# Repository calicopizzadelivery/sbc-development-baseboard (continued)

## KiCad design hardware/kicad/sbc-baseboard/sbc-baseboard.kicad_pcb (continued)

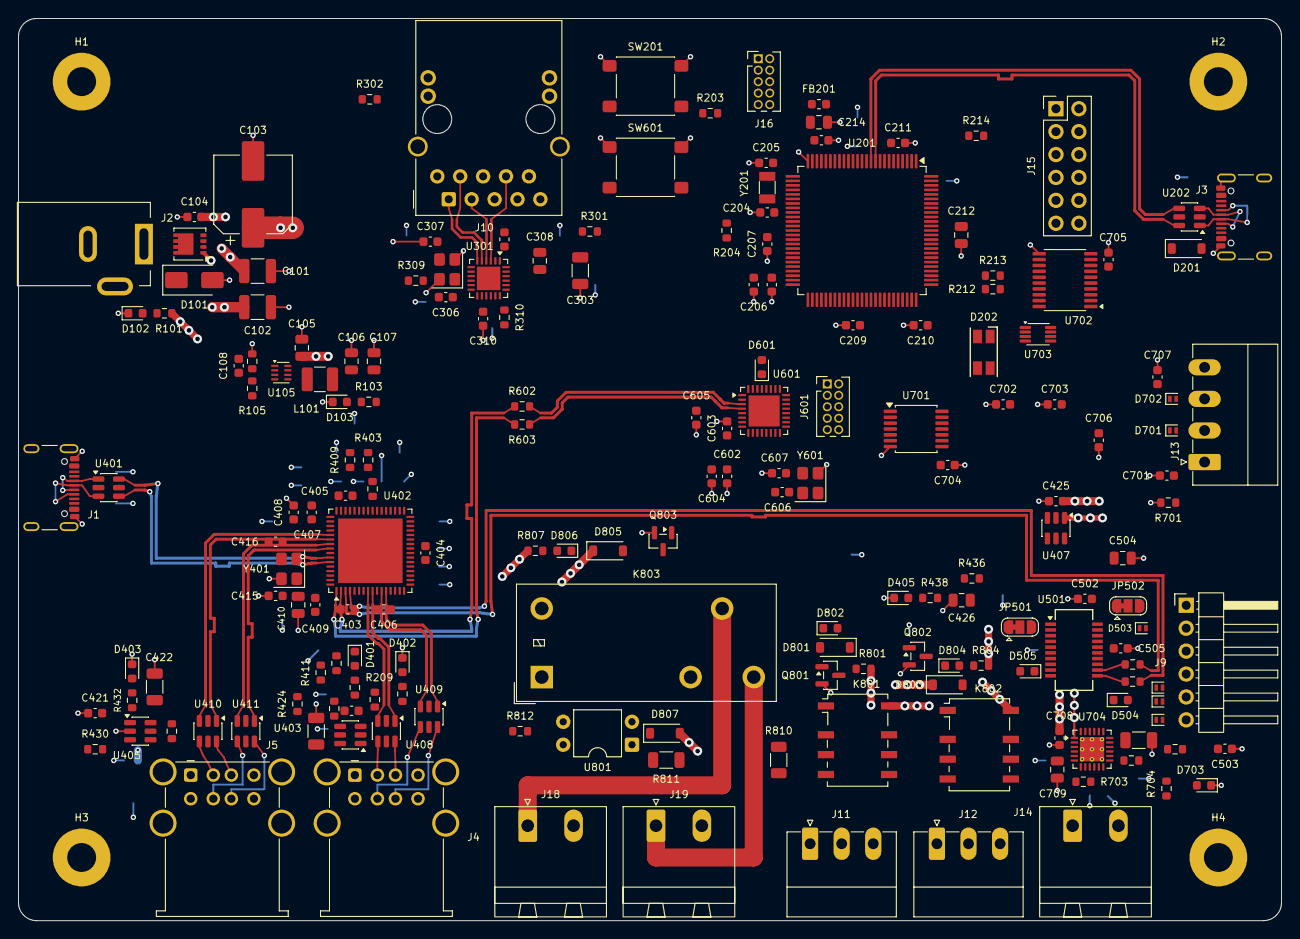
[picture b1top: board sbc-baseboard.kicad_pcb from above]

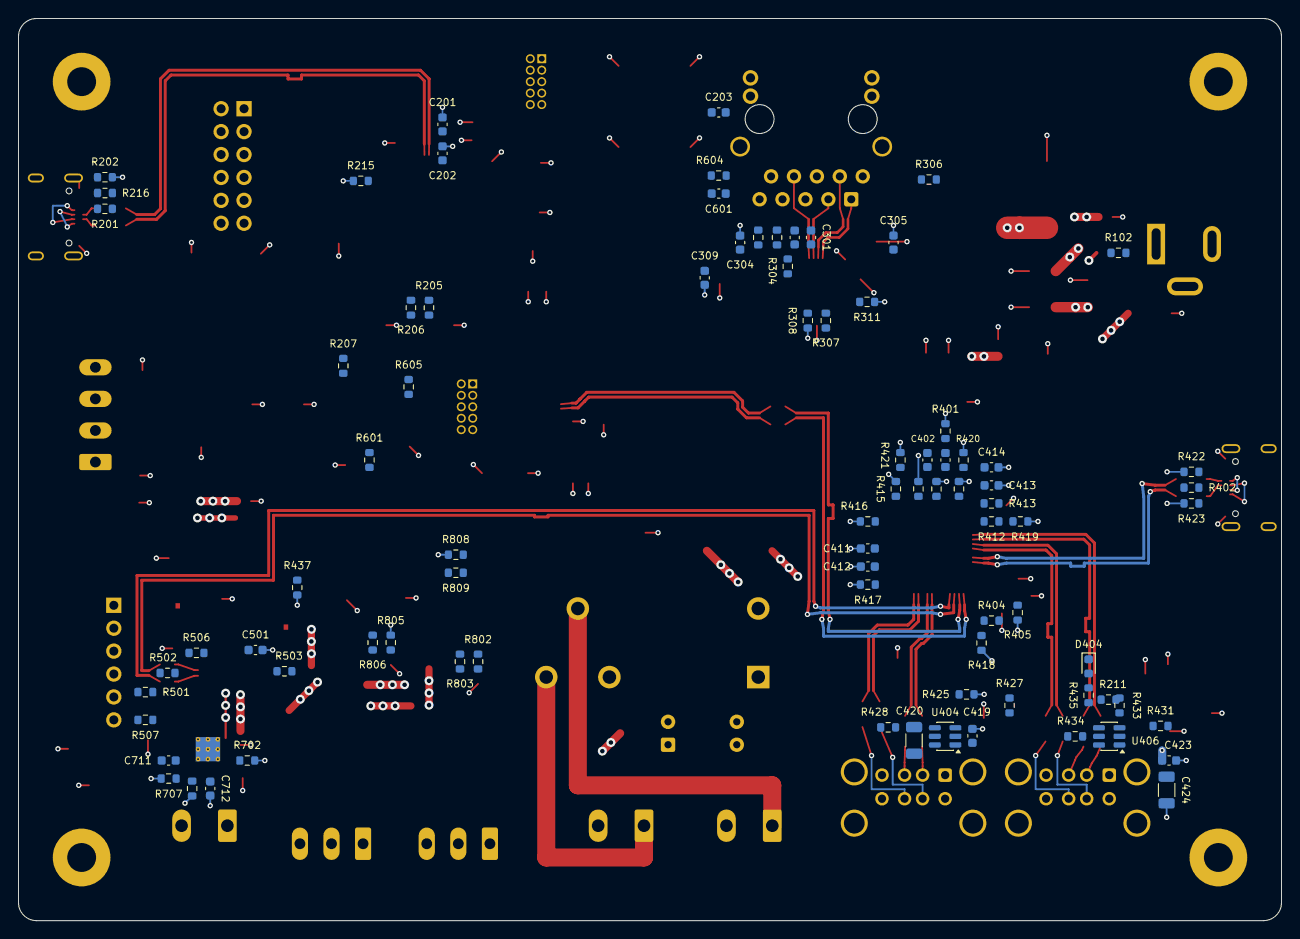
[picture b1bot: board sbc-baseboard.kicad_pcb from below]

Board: 6 copper layers, 140.0 x 100.0 mm, 271 parts (84 on the bottom side), 222 nets.

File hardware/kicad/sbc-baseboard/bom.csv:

"Reference","Value","Footprint","QUANTITY"
"C101,C102","47u/10V","Capacitor_SMD:C_1210_3225Metric","2"
"C103","100u/10V","Capacitor_SMD:CP_Elec_8x10.5","1"
"C104,C206,C207,C208,C209,C210,C211,C213,C301,C302,C305,C309,C310,C403,C404,C405,C406,C407,C408,C409,C412,C414,C417,C419,C421,C423,C425,C501,C505,C601,C603,C604,C701,C702,C703,C704,C705,C706,C707,C708","100n","Capacitor_SMD:C_0603_1608Metric","40"
"C105,C212,C214,C426,C504,C709","10u","Capacitor_SMD:C_0805_2012Metric","6"
"C106,C107,C308","22u","Capacitor_SMD:C_0805_2012Metric","3"
"C108","120p","Capacitor_SMD:C_0603_1608Metric","1"
"C201,C202,C304,C602,C605","2u2","Capacitor_SMD:C_0603_1608Metric","5"
"C203,C401,C402,C411,C413","1u","Capacitor_SMD:C_0603_1608Metric","5"
"C204,C205","12p","Capacitor_SMD:C_0603_1608Metric","2"
"C303","1n/2kV","Capacitor_SMD:C_1206_3216Metric","1"
"C306,C307","22p","Capacitor_SMD:C_0603_1608Metric","2"
"C410","4u7","Capacitor_SMD:C_0805_2012Metric","1"
"C415,C416","33p","Capacitor_SMD:C_0603_1608Metric","2"
"C418,C420,C422,C424,C710","22u","Capacitor_SMD:C_1206_3216Metric","5"
"C502,C503","47p","Capacitor_SMD:C_0603_1608Metric","2"
"C606,C607","18p","Capacitor_SMD:C_0603_1608Metric","2"
"C711","1n","Capacitor_SMD:C_0603_1608Metric","1"
"C712","10n","Capacitor_SMD:C_0603_1608Metric","1"
"D101","SMAJ5.0A","Diode_SMD:D_SMA","1"
"D102,D103","LED AMBER","LED_SMD:LED_0603_1608Metric","2"
"D201","BAT54","Diode_SMD:D_SOD-123","1"
"D202","RGB heartbeat","LED_SMD:LED_RGB_1210","1"
"D401,D402,D403,D404,D405,D504,D505,D601,D703","LED GREEN","LED_SMD:LED_0603_1608Metric","9"
"D501,D502,D503,D506,D701,D702","PESD5V0S1UL","Diode_SMD:D_SOD-882","6"
"D801,D803,D805,D807","1N4148W","Diode_SMD:D_SOD-123","4"
"D802,D804,D806","LED RED","LED_SMD:LED_0603_1608Metric","3"
"FB201,FB301","600R@100MHz","Inductor_SMD:L_0603_1608Metric","2"
"H1,H2,H3,H4","M3","MountingHole:MountingHole_3.2mm_M3_Pad","4"
"J1","USB-C upstream","calico:USB_C_Receptacle_GCT_USB4105-xx-A_16P_TopMnt_Horizontal_PegClear","1"
"J2","5 V in, 2.5 mm","Connector_BarrelJack:BarrelJack_Kycon_KLDX-0202-xC_Horizontal","1"
"J3","USB-C HID to target","calico:USB_C_Receptacle_GCT_USB4105-xx-A_16P_TopMnt_Horizontal_PegClear","1"
"J4,J5","USB-A x2","Connector_USB:USB_A_Wuerth_61400826021_Horizontal_Stacked","2"
"J9","FTDI header","Connector_PinHeader_2.54mm:PinHeader_1x06_P2.54mm_Horizontal","1"
"J10","RJ45 magjack 10/100","Connector_RJ:RJ45_Kycon_G7LX-A88S7-BP-xx_Horizontal","1"
"J11,J12","COM/NO/NC","Connector_Phoenix_MC:PhoenixContact_MC_1,5_3-G-3.5_1x03_P3.50mm_Horizontal","2"
"J13","Console","Connector_Phoenix_MC:PhoenixContact_MC_1,5_4-G-3.5_1x04_P3.50mm_Horizontal","1"
"J14","+5V_TGT out","Connector_Phoenix_MSTB:PhoenixContact_MSTBA_2,5_2-G-5,08_1x02_P5.08mm_Horizontal","1"
"J15","GPIO + I2C","Connector_PinHeader_2.54mm:PinHeader_2x06_P2.54mm_Vertical","1"
"J16","SWD","Connector_PinHeader_1.27mm:PinHeader_2x05_P1.27mm_Vertical","1"
"J18","PSU in (isolated)","Connector_Phoenix_MSTB:PhoenixContact_MSTBA_2,5_2-G-5,08_1x02_P5.08mm_Horizontal","1"
"J19","PSU out (isolated)","Connector_Phoenix_MSTB:PhoenixContact_MSTBA_2,5_2-G-5,08_1x02_P5.08mm_Horizontal","1"
"J601","SWD (K20)","Connector_PinHeader_1.27mm:PinHeader_2x05_P1.27mm_Vertical","1"
"JP501","RTS/DTR","Jumper:SolderJumper-3_P1.3mm_Bridged12_RoundedPad1.0x1.5mm","1"
"JP502","VCC 5V/3V3","Jumper:SolderJumper-3_P1.3mm_Bridged12_RoundedPad1.0x1.5mm","1"
"K801,K802","G6K-2F-Y DC5","Relay_SMD:Relay_DPDT_Omron_G6K-2F-Y","2"
"K803","JW1FSN-DC5V","Relay_THT:Relay_SPDT_Panasonic_JW1_FormC","1"
"L101","470n/4A","Inductor_SMD:L_1210_3225Metric","1"
"Q101","DMP3013SFV","Package_SON:Diodes_PowerDI3333-8","1"
"Q801,Q802","2N7002","Package_TO_SOT_SMD:SOT-23","2"
"Q803","AO3400A","Package_TO_SOT_SMD:SOT-23","1"
"R101,R309,R310,R426,R429,R432,R435,R438,R705,R803,R806,R809","1k","Resistor_SMD:R_0603_1608Metric","12"
"R102,R104,R216,R401,R402,R701,R802,R805,R808","100k","Resistor_SMD:R_0603_1608Metric","9"
"R103,R501,R502,R503,R507,R605","470","Resistor_SMD:R_0603_1608Metric","6"
"R105","453k","Resistor_SMD:R_0603_1608Metric","1"
"R201,R202,R422,R423","5.1k","Resistor_SMD:R_0603_1608Metric","4"
"R203,R204,R208,R209,R210,R211,R214,R308,R403,R405,R406,R407,R408,R409,R410,R411,R412,R413,R414,R415,R416,R417,R418,R419,R420,R421,R424,R427,R430,R433,R436,R506,R601,R604,R704,R706,R812","10k","Resistor_SMD:R_0603_1608Metric","37"
"R205,R206,R207,R301,R302","330","Resistor_SMD:R_0603_1608Metric","5"
"R212,R213","4.7k","Resistor_SMD:R_0603_1608Metric","2"
"R215","47k","Resistor_SMD:R_0603_1608Metric","1"
"R303,R304,R305,R306","75","Resistor_SMD:R_0603_1608Metric","4"
"R307,R602,R603","33","Resistor_SMD:R_0603_1608Metric","3"
"R311","6.49k 1%","Resistor_SMD:R_0603_1608Metric","1"
"R404","12.0k 1%","Resistor_SMD:R_0603_1608Metric","1"
"R425,R428,R431,R434,R437","23.7k","Resistor_SMD:R_0603_1608Metric","5"
"R504,R505","27","Resistor_SMD:R_0603_1608Metric","2"
"R702","75k","Resistor_SMD:R_0603_1608Metric","1"
"R703","196k","Resistor_SMD:R_0603_1608Metric","1"
"R707","20k","Resistor_SMD:R_0603_1608Metric","1"
"R708","6.04k 1%","Resistor_SMD:R_0603_1608Metric","1"
"R801,R804,R807","2.2k","Resistor_SMD:R_0603_1608Metric","3"
"R810,R811","1.8k","Resistor_SMD:R_1206_3216Metric","2"
"SW201","RESET","Button_Switch_SMD:SW_SPST_PTS645Sx43SMTR92","1"
"SW601","DAP RESET","Button_Switch_SMD:SW_SPST_PTS645Sx43SMTR92","1"
"U105","TPS62823DLC","Package_SON:Texas_VSON-HR-8_1.5x2mm_P0.5mm","1"
"U201","MK64FN1M0VLL12","Package_QFP:LQFP-100_14x14mm_P0.5mm","1"
"U202,U401,U408,U409,U410,U411","USBLC6-2SC6","Package_TO_SOT_SMD:SOT-23-6","6"
"U301","KSZ8081RNA","Package_DFN_QFN:QFN-24-1EP_4x4mm_P0.5mm_EP2.6x2.6mm","1"
"U402","USB2517","Package_DFN_QFN:QFN-64-1EP_9x9mm_P0.5mm_EP7.15x7.15mm","1"
"U403,U404,U405,U406,U407","TPS2553DBV","Package_TO_SOT_SMD:SOT-23-6","5"
"U501","FT231XS","Package_SO:SSOP-20_3.9x8.7mm_P0.635mm","1"
"U601","MK20DX128VFM5","Package_DFN_QFN:QFN-32-1EP_5x5mm_P0.5mm_EP3.45x3.45mm","1"
"U701","TXB0104PW","Package_SO:TSSOP-14_4.4x5mm_P0.65mm","1"
"U702","TXB0108PW","Package_SO:TSSOP-20_4.4x6.5mm_P0.65mm","1"
"U703","TXS0102DCU","Package_SO:VSSOP-8_2.3x2mm_P0.5mm","1"
"U704","TPS26630RGE","Package_DFN_QFN:Texas_RGE0024H_VQFN-24-1EP_4x4mm_P0.5mm_EP2.7x2.7mm_ThermalVias","1"
"U801","LTV-817","Package_DIP:DIP-4_W7.62mm","1"
"Y201","32.768kHz","Crystal:Crystal_SMD_3215-2Pin_3.2x1.5mm","1"
"Y301","25MHz","Crystal:Crystal_SMD_3225-4Pin_3.2x2.5mm","1"
"Y401","24MHz","Crystal:Crystal_SMD_3225-4Pin_3.2x2.5mm","1"
"Y601","8MHz","Crystal:Crystal_SMD_3225-4Pin_3.2x2.5mm","1"

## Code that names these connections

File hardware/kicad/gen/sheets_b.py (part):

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                 5: chain(Ser("R", "75", None), BusEnd("bs")), 8: chain(Ser("R", "75", None), BusEnd("bs")),
                 10: chain(Ser("R", "75", None), BusEnd("bs")), 9: chain(Ser("R", "75", None), BusEnd("bs")), "SH": P("GND")})
    bus_join(s, "bs", then=chain(Ser("C", "1n/2kV", None, fp=FP["C1206"]), P("GND")), sx=-1)
    # MDIO pull-up 1.0 k and INTRP pull-up 1.0 k: both required by the KSZ8081 datasheet pin table
    fan(s, u, {10: chain(Pull("+3V3", "R", "1k", None), L("MDIO")), 11: L("MDC"), 12: L("RMII_RXD1"), 13: L("RMII_RXD0"), 15: L("RMII_CRS_DV"),
               16: chain(Ser("R", "33", None), L("RMII_CLK_50M")), 17: chain(Pull("GND", "R", "10k", None), L("RMII_RXER")),
               18: chain(Pull("+3V3", "R", "1k", None), L("PHY_INT_N")), 19: L("RMII_TXEN"), 20: L("RMII_TXD0"), 21: L("RMII_TXD1"), 24: L("K64_RESET_N"),
               8: End("xi"), 7: End("xo"),                                   # the crystal hangs below, drawn by crystal()
               3: To("rd-"), 4: To("rd+"), 5: To("td-"), 6: To("td+"), 9: Pull("GND", "R", "6.49k 1%", None), 23: To("ledg_k"),
               22: P("GND"), 25: P("GND")}, align={"L": "top"})
    for pin, net in (("6", "ETH_TD_P"), ("5", "ETH_TD_N"), ("4", "ETH_RD_P"), ("3", "ETH_RD_N")):   # the MDI pairs, named for the router: class ETH, 100 ohm
        s.label(net, s.lane_end[(u.ref, pin)], rot=0)
    jog(s, u, 2, "+3V3A_PHY", up=5.08, over=10.16)
    jog(s, u, 14, "+3V3", up=2.54, over=12.7)
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    pd10 = lambda: chain(Ser("R", "10k", None), P("GND"))
    pu10 = lambda: Pull("+3V3", "R", "10k", None)
    jx = join_pins(s, j1, ["A6", "B6"], length=10.16)[0]; join_pins(s, j1, ["A7", "B7"], length=10.16)   # room for the pair's labels on the lower stubs
    atts = {59: End("usbup_dp"), 58: End("usbup_dm"), 44: chain(Pull("GND", "R", "100k", None), Pull("GND", "C", "1u", None), Ser("R", "100k", None), L("J1_VBUS")),     # VBUS_DET divider as on EVB-USB2517: 100k/100k with 1 uF, at the pin that reads it
            61: End("xtal1"), 60: End("xtal2"),                                # the crystal hangs below, drawn by crystal()
            43: chain(Tag("HUB_RESET_N", None, step=35.56), Reset("+3V3", "10k", "1u")),      # the R/C column lands beyond the VBUS_DET divider's capacitor and its text
            63: chain(Ser("R", "12.0k 1%", None), P("GND")), 19: P("GND"),
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        dp, dm = {1: (9, 8), 2: (12, 11), 3: (54, 53), 4: (56, 55)}[n]
        atts[dp] = chain(Tag(f"HUB_DN{n + 3}_P", None), Conn(esd, 1)); atts[dm] = chain(Tag(f"HUB_DN{n + 3}_N", None), Conn(esd, 3))   # I/O1 is the D+ row, I/O2 the D- row; hub ports 4..7
    ends = fan(s, u, atts, align={"L": "top"}, channels={"R": 270.51}, turn_at={"L": 118.11})    # left rows stay on their pins for U401; routes clear the cap ladder and pull-ups; the strap lanes turn clear of the bottom ladders
    for pin, net in (("58", "HUB_UP_N"), ("59", "HUB_UP_P")):          # the upstream pair to U401, named for the router: at the lane end, text toward the hub
        s.label(net, s.lane_end[(u.ref, pin)], 0)
    bus_join(s, "strap_gnd", then=P("GND"), sx=1)
    top_bus(s, u, [46, 24, 64, 5, 10, 52, 57], "+3V3", caps_left=[("100n", None)] * 4, caps_right=[("100n", None)] * 3 + [("4u7", FP["C0805"])],
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    top_caps(s, u, 62, [("1u", None), ("100n", None)], height=12.7, sx=1)
    crystal(s, u, "xtal1", "xtal2", "Y401", "24MHz", FP["XTAL4"], "33p")
    fan(s, j1, {"A6": Skip(), "B6": Skip(), "A7": Skip(), "B7": Skip(),
                "A4": chain(Flag(None), Gap(22.86), L("J1_VBUS")),                  # plain stretch: U401 taps it, the divider sits at U402 pin 44
                "A5": chain(Ser("R", "5.1k", None, step=12.7), P("GND")),       # the upper GND lands past the lower row's end
                "B5": chain(Ser("R", "5.1k", None, step=7.62), P("GND")), "A1": P("GND"), "SH": P("GND")}, align="top")
    # the joined pairs continue straight into the ESD array from their join
    for pin, row in (("1", j1.pin("B7")[1]), ("3", j1.pin("A6")[1])):
        s.wire((jx, row), esd0.pin(pin)); s.junction((jx, row))
    fan(s, esd0, {6: To("usbup_dm"), 4: To("usbup_dp"), 2: P("GND")})
    for pin, net in (("B7", "J1_D_N"), ("B6", "J1_D_P")):              # the connector side of the pair, named for the router: on the lower stub of each joined pair
        s.label(net, j1.pin(pin), 0)     # I/O1 sits on the D- row, I/O2 on D+
    vx, vy = esd0.pin("5")                                              # VBUS pin straight up onto J1's VBUS lane
    vb = (vx, j1.pin("A4")[1])
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    s.project_lib = plib
    s.note(["FTDI HEADER J9", "Pinout = Adafruit FTDI Friend (the TTL-232R order): 1 GND (blk)  2 CTS (brn)  3 VCC (red)  4 TXD (org)  5 RXD (yel)  6 RTS/DTR (grn).",
            "TXD/RXD named from the FT231X side: TXD drives the target's RX. 3.3 V levels only; 1.8 V consoles use J13.",
            "JP501: pin 6 = RTS# (A-C, bridged by default) or DTR# (cut, bridge B-C). JP502: pin 3 VCC = FTDI_VBUS 5 V (A-C, default) or 3V3OUT 3.3 V / 50 mA (B-C).",
            "VCC comes from the TPS2553 on the hub sheet (FTDI_VBUS): FTDI CYCLE power-cycles the bridge without a replug.",
            "CBUS defaults: CBUS1 = RXLED#, CBUS2 = TXLED# (factory MTP); change with FT_PROG if ever needed."], (16, 17), 1.5)
    u = s.add("Interface_USB", "FT231XS", "U501", "FT231XS", (150, 120), footprint="Package_SO:SSOP-20_3.9x8.7mm_P0.635mm")
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               2: Conn(jp, 1, stub=5.08), 1: Conn(jp, 3, stub=5.08), 10: led(), 17: led(),
               # FT231X datasheet figure 6.1: 27 R in series, 47 pF to ground on the bus side
               11: chain(Ser("R", "27", None), Pull("GND", "C", "47p", None), L("HUB_DN2_P")), 12: chain(Ser("R", "27", None), Pull("GND", "C", "47p", None), L("HUB_DN2_N")), 13: chain(Gap(38.1), Pull("GND", "C", "100n", None), Gap(7.62), P("FTDI_3V3")),   # its name clear of the VCC ladder's rail
               14: Pull("FTDI_3V3", "R", "10k", None), 3: P("FTDI_3V3"), 6: P("GND"), 16: P("GND")}, reach={"L": 19.05}, align={"L": "top"})   # 3V3OUT: its cap and rail far out on a lane that stays on its pin, clear of the VCC decoupling above
    for pin, net in (("11", "FTDI_USB_P"), ("12", "FTDI_USB_N")):        # the chip side of the pair, named for the router: at the lane end, text toward the chip
        s.label(net, s.lane_end[(u.ref, pin)], 0 if u.pin_dir(pin) == "L" else 180)
    top_caps(s, u, 15, [("10u", FP["C0805"]), ("100n", None)], height=15.24, sx=-1, rail="FTDI_VBUS")
    fan(s, jp, {2: chain(Ser("R", "470", None), TVS(), Conn(j9, 6))})
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    for pin in (6, 7, 8): s.pin_nc(j, str(pin))
    fan(s, u, {12: Conn(j, 4), 15: Conn(j, 2), 16: Pull("K20_3V3", "R", "10k", None),
               17: End("xtalin"), 18: End("xtalout"),                           # the crystal hangs below, drawn by crystal()
               19: chain(Tag("K20_RESET_N", None), Reset("K20_3V3", "10k", "100n", "DAP RESET", sw_fp=FP["SW"])),   # J601 pin 10 carries the same label
               3: chain(Ser("R", "33", None), End("dn1_p")), 4: chain(Ser("R", "33", None), End("dn1_n")), 5: chain(Pull("GND", "C", "2u2", None), P("K20_3V3")),
               21: L("K64_RESET_N"), 24: L("K64_UART0_TX"), 25: L("K64_UART0_RX"), 26: L("SWCLK"), 27: L("SWDIO"), 28: L("SWDIO"),   # PTC6 drives, PTC7 reads SWDIO (DAPLink k20dx, FRDM-K64F)
               29: chain(Ser("D", "LED GREEN", None, lib="Device", name="LED", near="1", fp=FP["LED"]), Ser("R", "470", None), P("K20_3V3")),
               11: P("K20_3V3"), 2: P("GND"), 8: P("GND"), 33: P("GND")}, reach={"L": 21.59})   # room on the pair lanes for the chip-side labels before the lanes' turns
    for pin, net in (("3", "K20_USB_P"), ("4", "K20_USB_N")):            # the chip side of the pair, named for the router
        s.label(net, s.lane_end[(u.ref, pin)], 0)
    for key, net in (("dn1_p", "HUB_DN1_P"), ("dn1_n", "HUB_DN1_N")):      # the hub side of the pair, beyond the series resistors
        s.label(net, End.registry[(id(s), key)][0], 180)
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
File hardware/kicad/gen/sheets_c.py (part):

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    s.project_lib = plib
    s.note(["TARGET-FACING I/O",
            "VREF_TGT comes from the target on J13.1 / J15.1 and sets the level of every translator (TXB0104/TXB0108/TXS0102).",
            "OE pins follow VREF_TGT: with the target off the translators are high-impedance. J15 GPIO are push-pull (TXB).",
            "TXS0102 instead of PCA9306: works with VREF_TGT equal to 3.3 V (PCA9306 needs VREF2 > VREF1). Range 1.65-3.6 V.",
            "TPS26630: ILIM 6.04k -> 3 A (RILIM = 18 kOhm.A / IOL; 3.65k -> 5 A until 2026-10-10, when the 20 W inlet set the budget), UVLO 196k/75k -> 4.3 V, OVP/MODE/PGTH to GND (latch-off). IMON 20k -> 1.7 V at 3 A into PTB2."], (16, 17), 1.5)
    j13 = s.add("Connector_Generic", "Conn_01x04", "J13", "Console", (40, 68), 180, footprint=FP["PH4"])
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    top_caps(s, u1, 1, [("100n", None)], height=7.62, sx=-1, up=True, rail="VREF_TGT")
    top_caps(s, u1, 14, [("100n", None)], height=7.62, sx=1, up=True, rail="+3V3")
    # GPIO + I2C breakout (labelled, as a breakout header is)
    fan(s, j15, {1: P("VREF_TGT"), 2: P("GND"), 3: L("TGT_GPIO1"), 4: L("TGT_GPIO2"), 5: L("TGT_GPIO3"), 6: L("TGT_GPIO4"),
                 7: L("TGT_GPIO5"), 8: L("TGT_GPIO6"), 9: L("J15_SDA"), 10: L("J15_SCL"), 11: P("GND"), 12: P("GND")})
    fan(s, u2, {1: L("TGT_GPIO1"), 3: L("TGT_GPIO2"), 4: L("TGT_GPIO3"), 5: L("TGT_GPIO4"), 6: L("TGT_GPIO5"), 7: L("TGT_GPIO6"), 10: P("VREF_TGT"),
                20: L("GPIO1"), 18: L("GPIO2"), 17: L("GPIO3"), 16: L("GPIO4"), 15: L("GPIO5"), 14: L("GPIO6"),
                11: P("GND")})
    top_caps(s, u2, 2, [("100n", None)], height=7.62, sx=-1, up=True, rail="VREF_TGT")
    top_caps(s, u2, 19, [("100n", None)], height=7.62, sx=1, up=True, rail="+3V3")
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                8: chain(Pull("+5V", ("Diode", "1N4148W", "1"), "1N4148W", None, fp=FP["SOD123"]), PullLED(RED, "2.2k", None, rail="+5V"), Conn(q3, 3)),
                6: End("psu_in"), 4: End("psu_out")})                       # the contacts' lanes end here; J18/J19 route to them
    fan(s, q3, {1: chain(Pull("GND", "R", "100k", None), Ser("R", "1k", None), L("RLY_PSU_DRV")), 2: P("GND")})
    fan(s, j18, {1: To("psu_in"), 2: P("PSU_GND")}, channels={"L": 278.13}); fan(s, j19, {1: To("psu_out"), 2: P("PSU_GND")}, channels={"L": 278.13})   # routes turn clear of the net labels
    for ref, net in (("J18", "PSU_VP"), ("J19", "PSU_VOUT")):               # the passthrough nets: named, and flagged as the 3 A class
        e = s.lane_end[(ref, "1")]; s.label(net, e, 180); s.netclass_flag("PSU_3A", e, 90)
    # the opto's LED nets are named so they join the isolated class (their creepage rule), as PSU_SENSE
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
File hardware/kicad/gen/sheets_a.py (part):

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    for pin, row in (("3", j3.pin("B7")[1]), ("1", j3.pin("A6")[1])):
        s.wire((jx, row), esd.pin(pin)); s.junction((jx, row))
    fan(s, esd, {2: P("GND")})
    for pin, net in (("B7", "J3_D_N"), ("B6", "J3_D_P")):              # the connector side of the pair, named for the router: on the lower stub of each joined pair
        s.label(net, j3.pin(pin), 0)
    vx, vy = esd.pin("5")                                               # VBUS pin straight up onto J3's VBUS lane
    vb = (vx, j3.pin("A4")[1])
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        82: chain(Tag("I2C1_SCL", None, step=21.59), Ser("R", "4.7k", None), BusEnd("pu_bus")), 83: chain(Tag("I2C1_SDA", None, step=21.59), Ser("R", "4.7k", None), BusEnd("pu_bus")),
        84: L("FTDI_EN"), 85: chain(Tag("FTDI_FAULT_N", None, step=21.59), Ser("R", "10k", None), BusEnd("pu_bus")), 86: L("TGT_EN"), 87: L("TGT_FAULT_N"),
        90: L("RLY1_DRV"), 91: L("RLY2_DRV"), 92: L("RLY_PSU_DRV"),
        93: L("GPIO1"), 94: L("GPIO2"), 95: L("GPIO3"), 96: L("GPIO4"), 97: L("GPIO5"), 98: L("GPIO6"),
        99: chain(Pull("GND", "R", "47k", None), Ser("R", "100k", None), L("J3_VBUS")),      # VBUS sense divider at the ADC pin
    }, align={"L": "top"})
    for pin in ("31", "32", "57", "58", "59"):                        # I2C0 and the PD sink's lines, free since the PD inlet went (2026-10-10)
        s.pin_nc(u, pin)
    for pin, net in (("6", "K64_USB_P"), ("4", "K64_USB_N")):            # the K64 side of the pair, named for the router: at the ESD's pin end, text along the route
        s.label(net, esd.pin(pin), 0)
    # seven pull-ups to +3V3 on adjacent pins (four port /FAULT, FTDI /FAULT, I2C1 SCL/SDA): one column
    # of resistors to one rail symbol, as the strap buses are drawn. Hung one per lane they would stagger
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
